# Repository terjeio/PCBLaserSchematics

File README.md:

# PCBLaserSchematics

KiCad schematics and PCB designs for my [Laser PCB Exposer](https://github.com/terjeio/PCBLaserDesktopApp).

Related [firmware](https://github.com/terjeio/PCBLaserFirmvare) in a separate project.

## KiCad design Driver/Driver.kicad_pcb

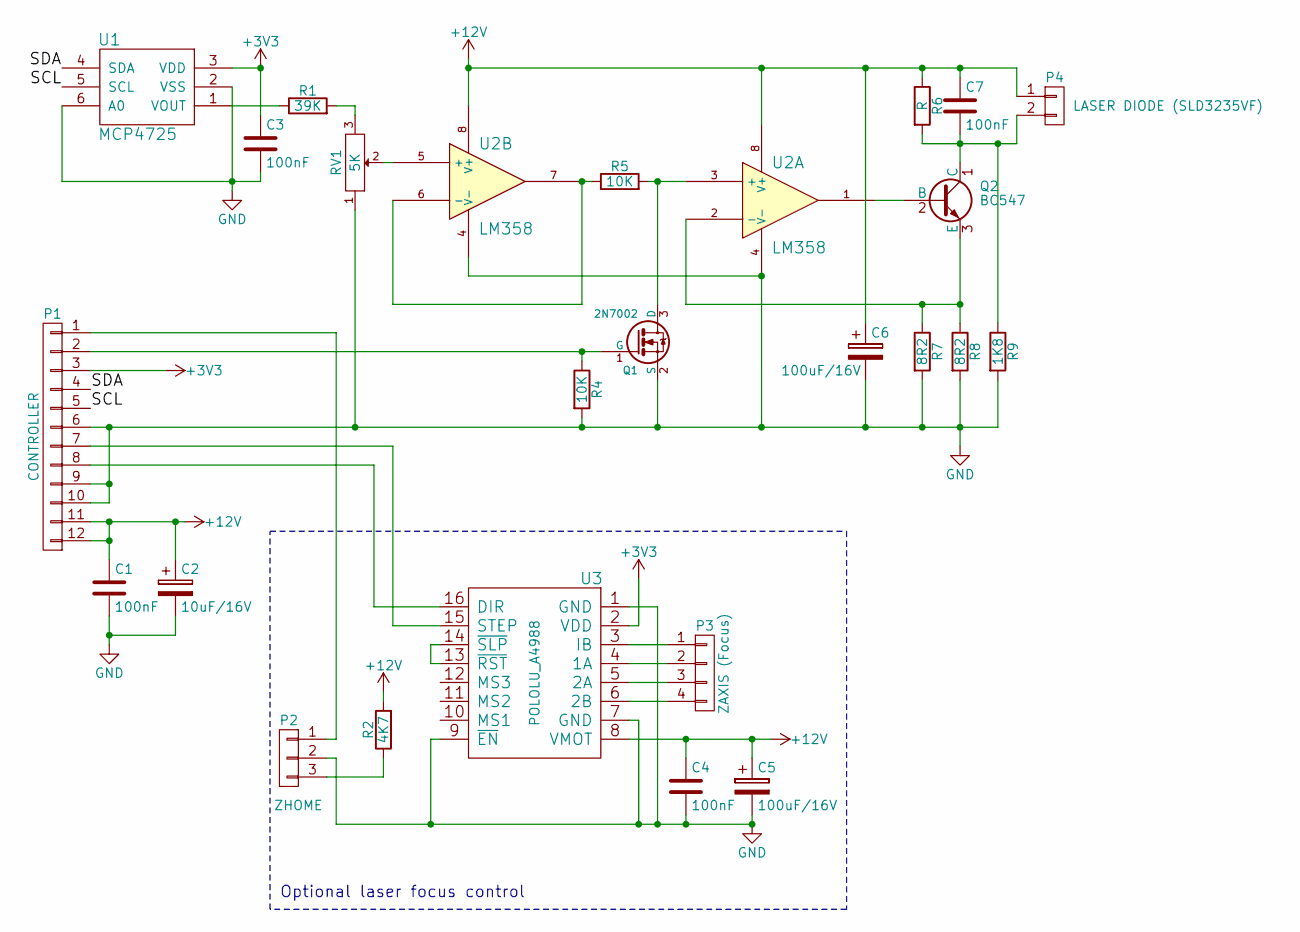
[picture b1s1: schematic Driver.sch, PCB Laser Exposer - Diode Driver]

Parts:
C1, C3, C4, C7: 100nF; C_1206
C2: 10uF/16V; TantalC_SizeA_EIA-3216_HandSoldering
C5: 100uF/16V; Elko_vert_11.5x8mm_RM3.5_CopperClear
C6: 100uF/16V; c_elec_5x4.5
P1: CONTROLLER; MOLEX_52271-1279
P2: ZHOME; Pin_Header_Straight_1x03
P3: ZAXIS (Focus); Pin_Header_Straight_1x04
P4: LASER DIODE (SLD3235VF); Pin_Header_Straight_1x02
Q1: 2N7002; SOT-23
Q2: BC547; TO-92_Molded_Narrow
R1: 39K; R_1206
R2: 4K7; R_1206
R4, R5: 10K; R_1206
R6: R; R_1206
R7, R8: 8R2; R_1206
R9: 1K8; R_1206
RV1: 5K; Potentiometer_Bourns_3296Y_3-8Zoll_Angular_ScrewUp
U1: MCP4725; SOT-23-6
U2: LM358; SO-8
U3: POLOLU_A4988; Polulu_A4988

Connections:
+3V3: C3.1, P1.3, U1.3 (VDD), U3.2 (VDD)
+12V: C1.1, C2.1, C4.1, C5.1, C6.1, C7.1, P1.11, P1.12, P4.1, R2.2, R6.1, U2.8 (V+), U3.8 (VMOT)
/SCL: P1.5, U1.5 (SCL)
/SDA: P1.4, U1.4 (SDA)
GND: C1.2, C2.2, C3.2, C4.2, C5.2, C6.2, P1.6, P1.9, P1.10, P1.13, P1.14, P2.2, Q1.2 (S), R4.2, R7.2, R8.2, R9.2, RV1.1, U1.2 (VSS), U1.6 (A0), U2.4 (V-), U3.1 (GND), U3.7 (GND), U3.9 (~EN)
unnamed: C7.2, P4.2, Q2.1 (C), R6.2, R9.1
unnamed: P1.1, P2.1
unnamed: P1.2, Q1.1 (G), R4.1
unnamed: P1.7, U3.15 (STEP)
unnamed: P1.8, U3.16 (DIR)
unnamed: P2.3, R2.1
unnamed: P3.1, U3.3 (IB)
unnamed: P3.2, U3.4 (1A)
unnamed: P3.3, U3.5 (2A)
unnamed: P3.4, U3.6 (2B)
unnamed: Q1.3 (D), R5.2, U2.3 (+)
unnamed: Q2.2 (B), U2.1
unnamed: Q2.3 (E), R7.1, R8.1, U2.2 (-)
unnamed: R1.1, U1.1 (VOUT)
unnamed: R1.2, RV1.3
unnamed: R5.1, U2.6 (-), U2.7
unnamed: RV1.2, U2.5 (+)
unnamed: U3.13 (~RST), U3.14 (~SLP)

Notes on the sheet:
Optional laser focus control

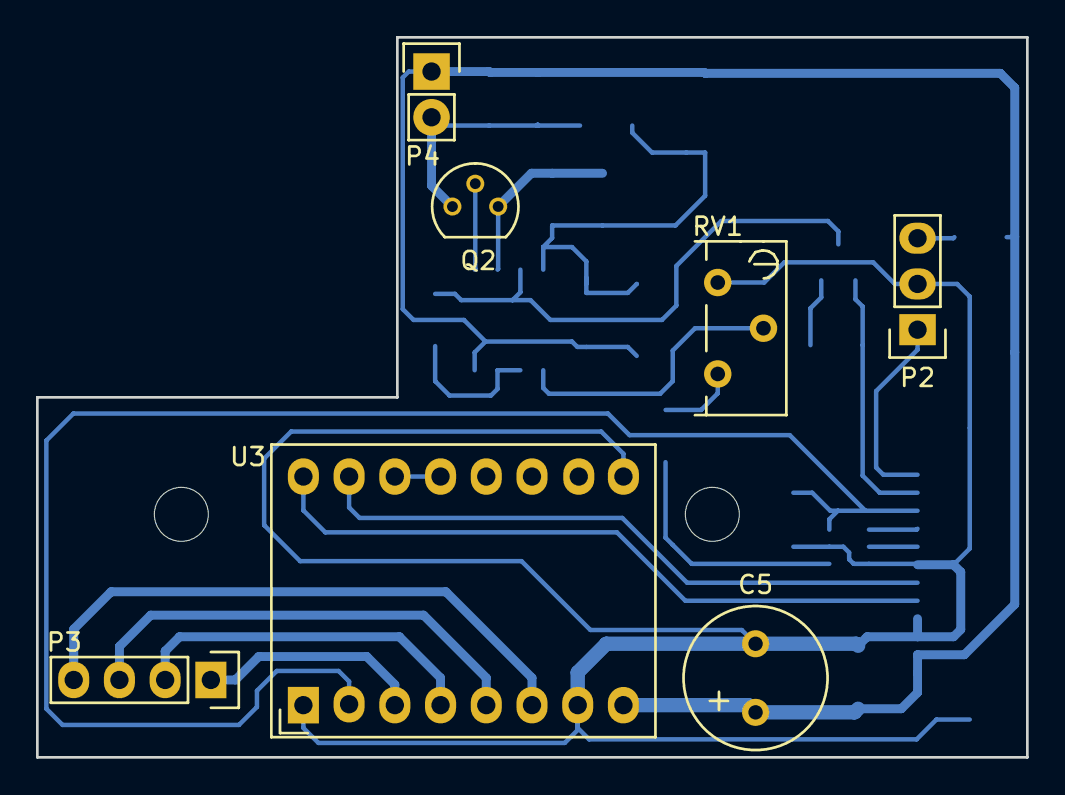
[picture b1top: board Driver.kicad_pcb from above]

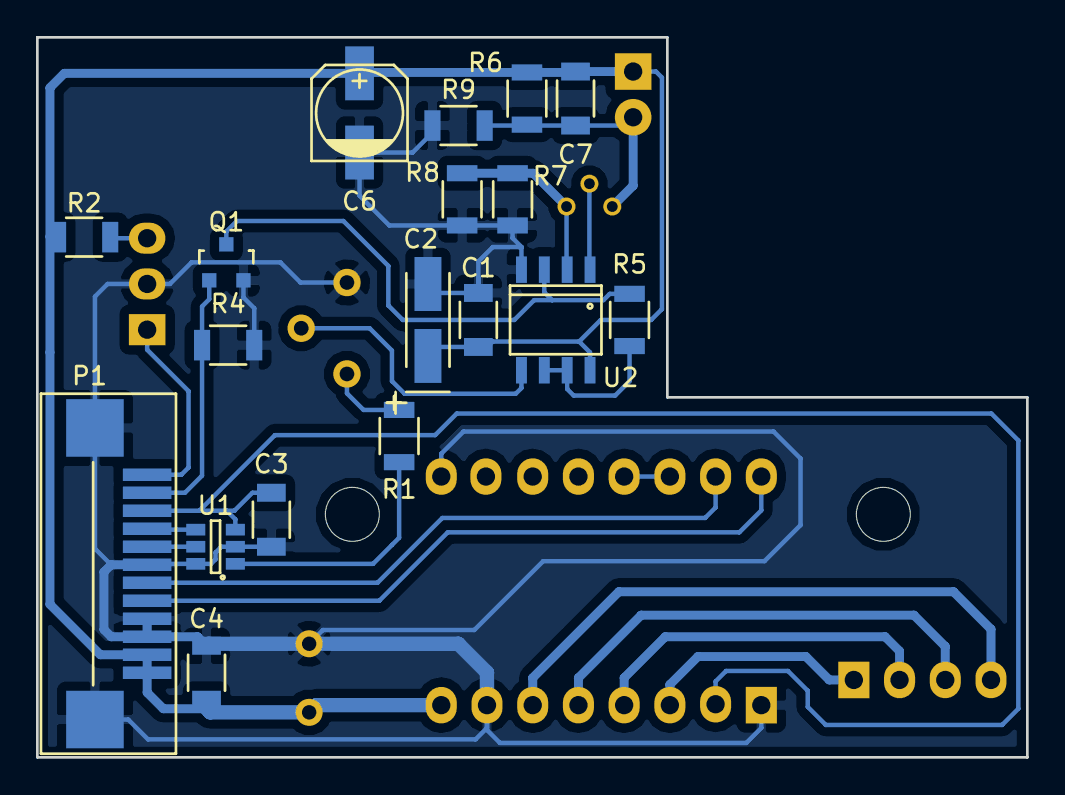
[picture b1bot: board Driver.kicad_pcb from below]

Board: 2 copper layers, 55.0 x 40.0 mm, 25 parts (18 on the bottom side), 23 nets.

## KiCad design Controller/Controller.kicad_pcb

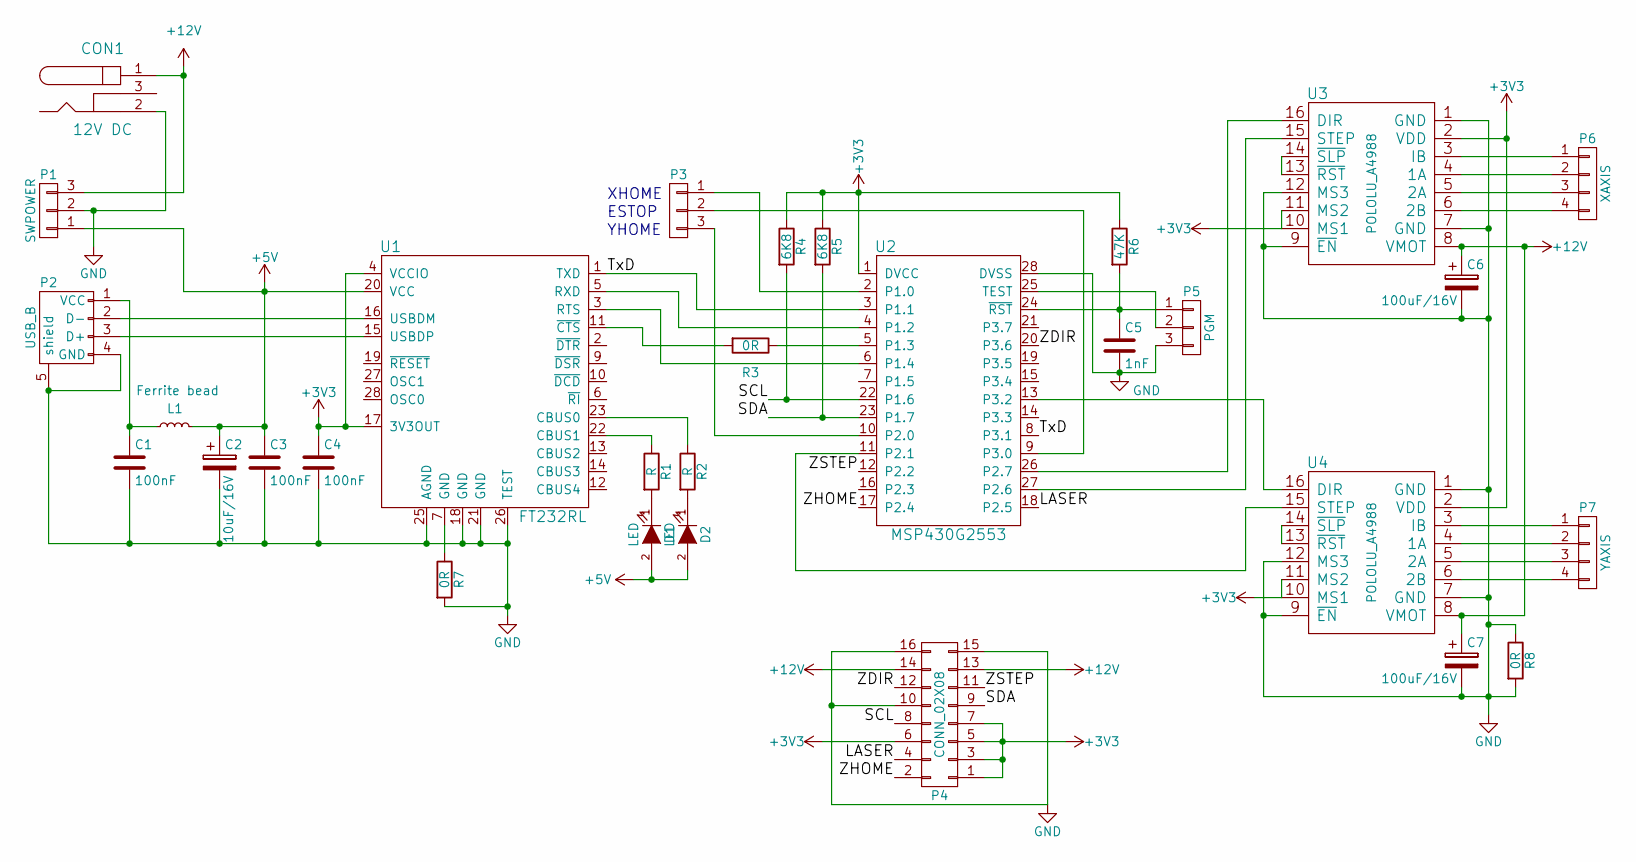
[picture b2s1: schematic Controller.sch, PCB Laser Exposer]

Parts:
C1, C3, C4: 100nF; C_1206
C2: 10uF/16V; TantalC_SizeA_EIA-3216_Reflow
C5: 1nF; C_1206
C6, C7: 100uF/16V; Elko_vert_11.5x8mm_RM3.5
CON1: 12V DC; BARREL_JACK
D1, D2: LED; LED-3MM
L1: Ferrite bead; Choke_Horizontal_RM10mm
P1: SWPOWER; Pin_Header_Straight_1x03
P2: USB_B
P3: CONN_01X03; Pin_Header_Straight_1x03
P4: CONN_02X08; Pin_Header_Angled_2x08
P5: PGM; Pin_Header_Straight_1x03
P6: XAXIS; CONN_PWR_4P
P7: YAXIS; CONN_PWR_4P
R1, R2: R; R_1206
R3, R7, R8: 0R; R_1206
R4, R5: 6K8; Resistor_Horizontal_RM10mm
R6: 47K; R_1206
U1: FT232RL; SSOP-28_5.3x10.2mm_Pitch0.65mm
U2: MSP430G2553; TSSOP28
U3, U4: POLOLU_A4988; Polulu_A4988

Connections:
+3V3: C4.1, P4.1, P4.3, P4.5, P4.6, P4.7, R4.1, R5.1, R6.1, U1.4 (VCCIO), U1.17 (3V3OUT), U2.1 (DVCC), U3.2 (VDD), U3.10 (MS1), U3.11 (MS2), U4.2 (VDD), U4.10 (MS1), U4.11 (MS2)
+5V: C2.1, C3.1, D1.2 (A), D2.2 (A), L1.2, P1.1, U1.20 (VCC)
+12V: C6.1, C7.1, CON1.1, P1.3, P4.13, P4.14, U3.8 (VMOT), U4.8 (VMOT)
/LASER: P4.4, U2.18 (P2.5)
/SCL: P4.8, R4.2, U2.22 (P1.6)
/SDA: P4.9, R5.2, U2.23 (P1.7)
/TxD: U1.1 (TXD), U2.3 (P1.1), U2.8 (P3.1)
/ZDIR: P4.12, U2.20 (P3.6)
/ZHOME: P4.2, U2.17 (P2.4)
/ZSTEP: P4.11, U2.12 (P2.2)
GND: C1.2, C2.2, C3.2, C4.2, C5.2, C6.2, C7.2, CON1.2, P1.2, P2.4 (GND), P2.5 (shield), P4.10, P4.15, P4.16, P5.3, R7.2, R8.1, R8.2, U1.18 (GND), U1.21 (GND), U1.25 (AGND), U1.26 (TEST), U2.28 (DVSS), U3.1 (GND), U3.7 (GND), U3.9 (~EN), U3.12 (MS3), U4.1 (GND), U4.7 (GND), U4.9 (~EN), U4.12 (MS3)
NC: U1.8 (NC)
unnamed: C1.1, L1.1, P2.1 (VCC)
unnamed: C5.1, P5.1, R6.2, U2.24 (~RST~)
unnamed: D1.1 (K), R1.2
unnamed: D2.1 (K), R2.2
unnamed: P2.2 (D-), U1.16 (USBDM)
unnamed: P2.3 (D+), U1.15 (USBDP)
unnamed: P3.1, U2.2 (P1.0)
unnamed: P3.2, U2.9 (P3.0)
unnamed: P3.3, U2.10 (P2.0)
unnamed: P5.2, U2.25 (TEST)
unnamed: P6.1, U3.3 (IB)
unnamed: P6.2, U3.4 (1A)
unnamed: P6.3, U3.5 (2A)
unnamed: P6.4, U3.6 (2B)
unnamed: P7.1, U4.3 (IB)
unnamed: P7.2, U4.4 (1A)
unnamed: P7.3, U4.5 (2A)
unnamed: P7.4, U4.6 (2B)
unnamed: R1.1, U1.22 (CBUS1)
unnamed: R2.1, U1.23 (CBUS0)
unnamed: R3.1, U2.5 (P1.3)
unnamed: R3.2, U1.11 (~CTS)
unnamed: R7.1, U1.7 (GND)
unnamed: U1.3 (RTS), U2.6 (P1.4)
unnamed: U1.5 (RXD), U2.4 (P1.2)
unnamed: U2.11 (P2.1), U4.15 (STEP)
unnamed: U2.13 (P3.2), U4.16 (DIR)
unnamed: U2.26 (P2.7), U3.16 (DIR)
unnamed: U2.27 (P2.6), U3.15 (STEP)
unnamed: U3.13 (~RST), U3.14 (~SLP)
unnamed: U4.13 (~RST), U4.14 (~SLP)

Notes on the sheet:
XHOME
YHOME
ESTOP

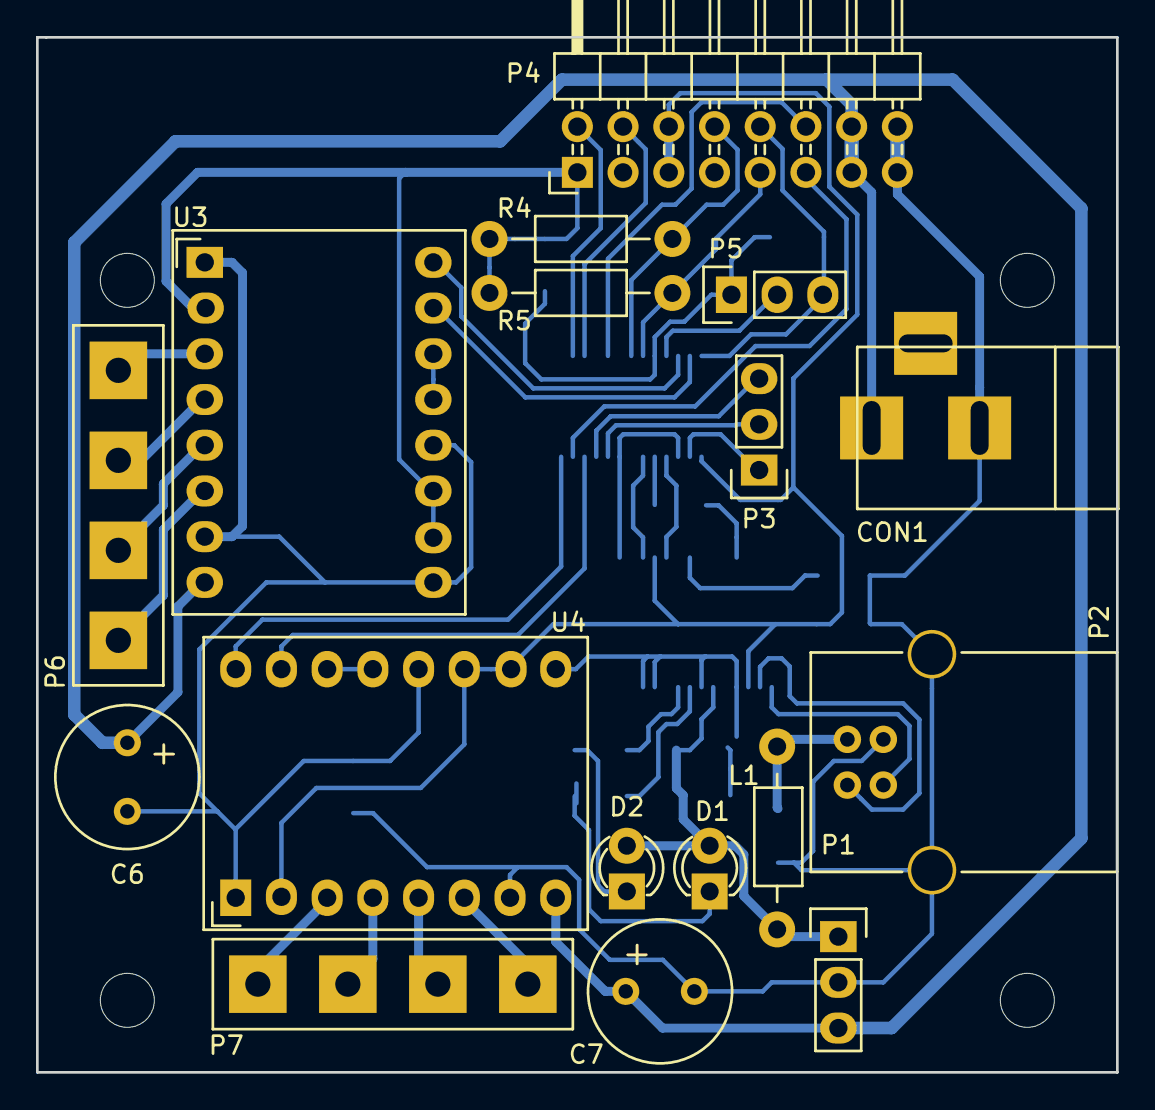
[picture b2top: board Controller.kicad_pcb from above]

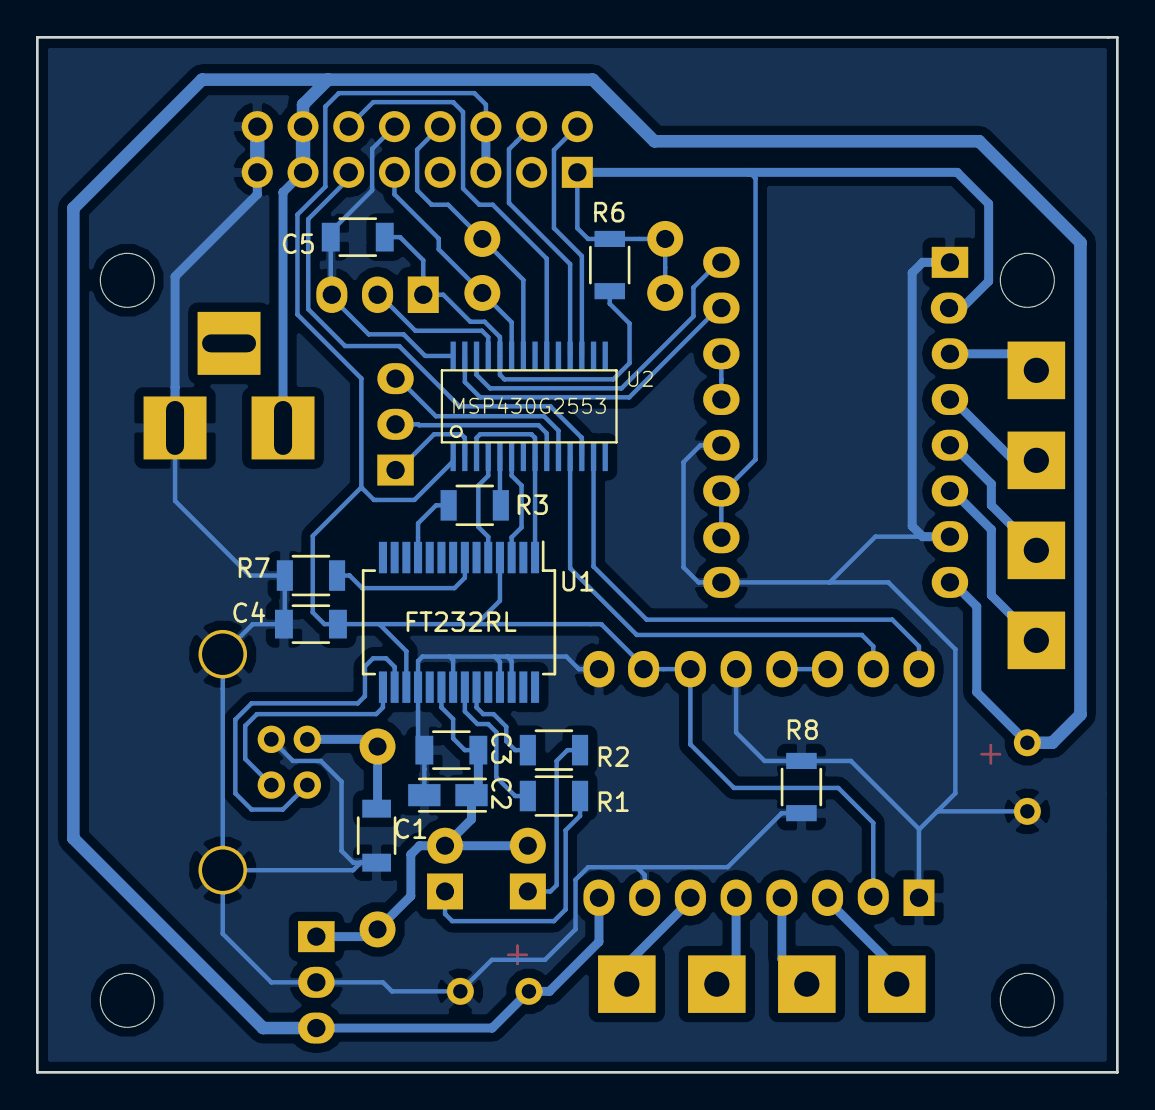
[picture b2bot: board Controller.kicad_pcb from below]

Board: 2 copper layers, 60.0 x 57.5 mm, 30 parts (13 on the bottom side), 42 nets.
